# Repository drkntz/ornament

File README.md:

# ornament
This project is a pic16f1832X-based project to run APA102-2020 and similar two-wire serial RGB LEDs. 

# Schematic rev 1

# PCB Layout rev 1

# PCB 3-D Model rev 1

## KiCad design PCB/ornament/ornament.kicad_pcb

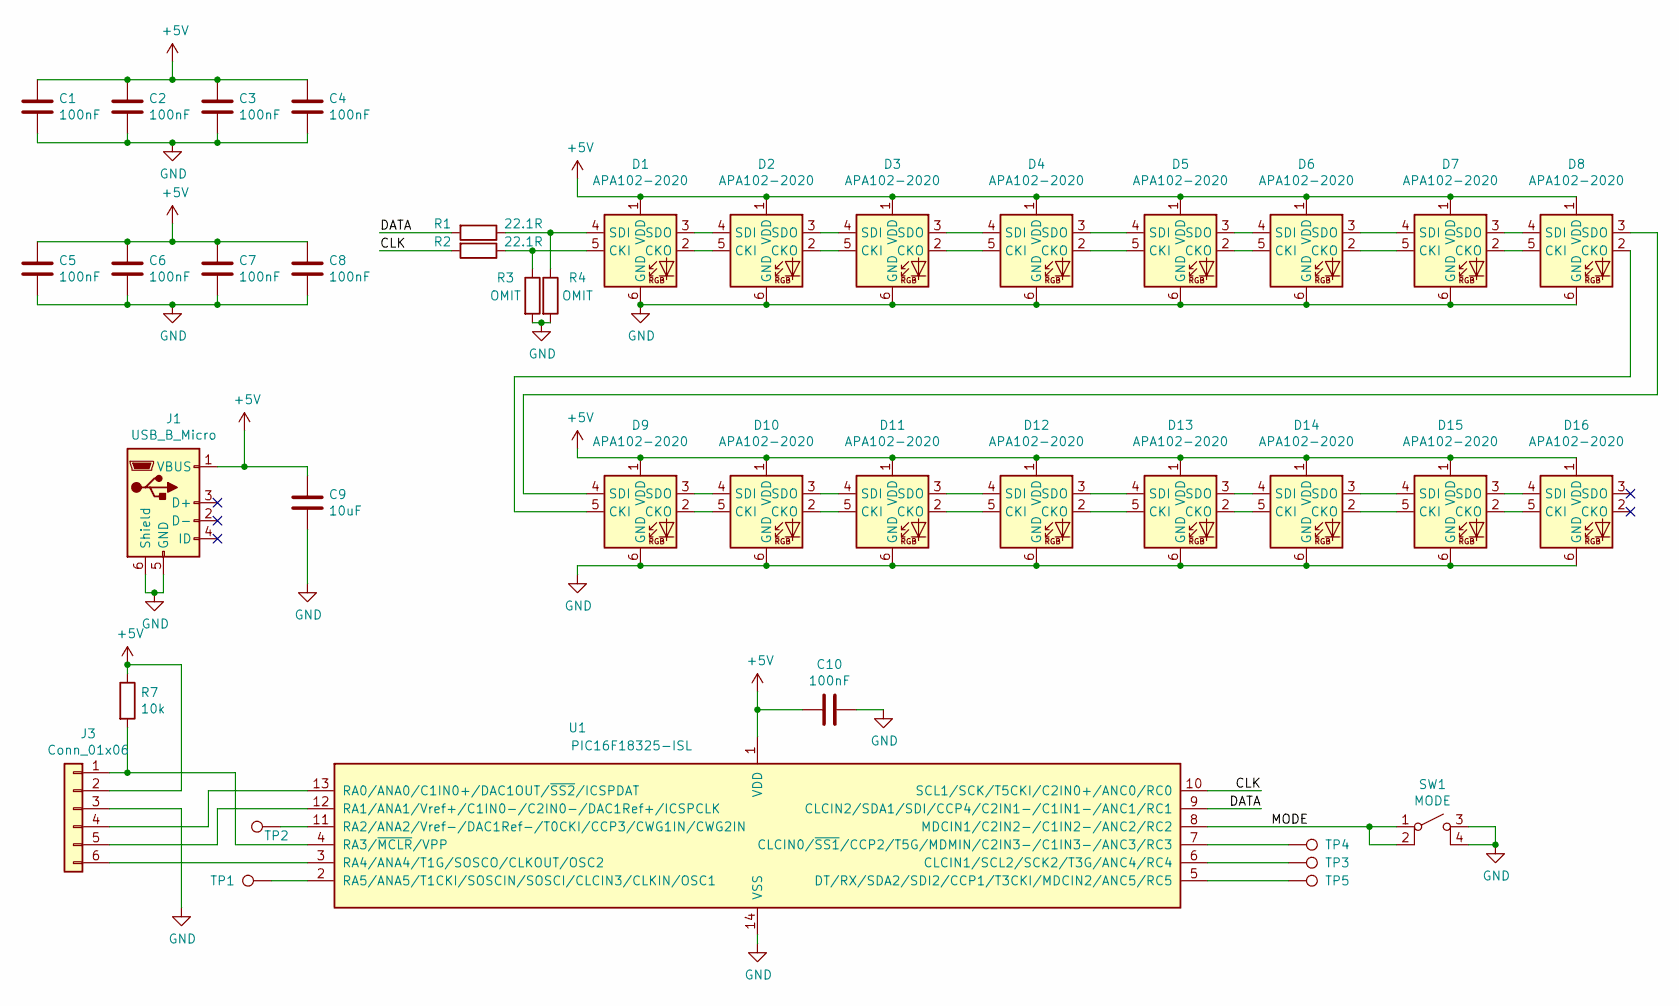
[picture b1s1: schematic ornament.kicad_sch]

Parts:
C1, C2, C3, C4, C5, C6, C7, C8, C10: 100nF; C_0805_2012Metric
C9: 10uF; C_0805_2012Metric
D1, D2, D3, D4, D5, D6, D7, D8, D9, D10, D11, D12, D13, D14, D15, D16: APA102-2020; LED-APA102-2020
J1: USB_B_Micro; USB_Micro-B_Molex-105017-0001
J3: Conn_01x06; Tag-Connect_TC2030-IDC-FP_2x03_P1.27mm_Vertical
R1, R2: 22.1R; R_0805_2012Metric
R3, R4: OMIT; R_0805_2012Metric
R7: 10k; R_0805_2012Metric
SW1: MODE; SW_SPST_Omron_B3FS-101xP
TP1: TP1; TestPoint_Plated_Hole_D2.0mm
TP2: TP2; TestPoint_Plated_Hole_D2.0mm
TP3: TP3; TestPoint_Plated_Hole_D2.0mm
TP4: TP4; TestPoint_Plated_Hole_D2.0mm
TP5: TP5; TestPoint_Plated_Hole_D2.0mm
U1: PIC16F18325-ISL; SOIC-14_3.9x8.7mm_P1.27mm

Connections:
+5V: C1.1, C2.1, C3.1, C4.1, C5.1, C6.1, C7.1, C8.1, C9.1, C10.2, D1.1 (VDD), D2.1 (VDD), D3.1 (VDD), D4.1 (VDD), D5.1 (VDD), D6.1 (VDD), D7.1 (VDD), D8.1 (VDD), D9.1 (VDD), D10.1 (VDD), D11.1 (VDD), D12.1 (VDD), D13.1 (VDD), D14.1 (VDD), D15.1 (VDD), D16.1 (VDD), J1.1 (VBUS), J3.2, R7.1, U1.1 (VDD)
/CLK: R2.2, U1.10 (SCL1/SCK/T5CKI/C2IN0+/ANC0/RC0)
/DATA: R1.2, U1.9 (CLCIN2/SDA1/SDI/CCP4/C2IN1-/C1IN1-/ANC1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)
/MODE: SW1.1 (A), SW1.2 (A1), U1.8 (MDCIN1/C2IN2-/C1IN2-/ANC2/RC2)
GND: C1.2, C2.2, C3.2, C4.2, C5.2, C6.2, C7.2, C8.2, C9.2, C10.1, D1.6 (GND), D2.6 (GND), D3.6 (GND), D4.6 (GND), D5.6 (GND), D6.6 (GND), D7.6 (GND), D8.6 (GND), D9.6 (GND), D10.6 (GND), D11.6 (GND), D12.6 (GND), D13.6 (GND), D14.6 (GND), D15.6 (GND), D16.6 (GND), J1.5 (GND), J1.6 (Shield), J3.3, R3.2, R4.2, SW1.3 (B), SW1.4 (B1), U1.14 (VSS)
unnamed: D1.2 (CKO), D2.5 (CKI)
unnamed: D1.3 (SDO), D2.4 (SDI)
unnamed: D1.4 (SDI), R1.1, R4.1
unnamed: D1.5 (CKI), R2.1, R3.1
unnamed: D2.2 (CKO), D3.5 (CKI)
unnamed: D2.3 (SDO), D3.4 (SDI)
unnamed: D3.2 (CKO), D4.5 (CKI)
unnamed: D3.3 (SDO), D4.4 (SDI)
unnamed: D4.2 (CKO), D5.5 (CKI)
unnamed: D4.3 (SDO), D5.4 (SDI)
unnamed: D5.2 (CKO), D6.5 (CKI)
unnamed: D5.3 (SDO), D6.4 (SDI)
unnamed: D6.2 (CKO), D7.5 (CKI)
unnamed: D6.3 (SDO), D7.4 (SDI)
unnamed: D7.2 (CKO), D8.5 (CKI)
unnamed: D7.3 (SDO), D8.4 (SDI)
unnamed: D8.2 (CKO), D9.5 (CKI)
unnamed: D8.3 (SDO), D9.4 (SDI)
unnamed: D10.2 (CKO), D11.5 (CKI)
unnamed: D10.3 (SDO), D11.4 (SDI)
unnamed: D9.3 (SDO), D10.4 (SDI)
unnamed: D9.2 (CKO), D10.5 (CKI)
unnamed: D11.2 (CKO), D12.5 (CKI)
unnamed: D11.3 (SDO), D12.4 (SDI)
unnamed: D12.2 (CKO), D13.5 (CKI)
unnamed: D12.3 (SDO), D13.4 (SDI)
unnamed: D13.2 (CKO), D14.5 (CKI)
unnamed: D13.3 (SDO), D14.4 (SDI)
unnamed: D14.2 (CKO), D15.5 (CKI)
unnamed: D14.3 (SDO), D15.4 (SDI)
unnamed: D15.2 (CKO), D16.5 (CKI)
unnamed: D15.3 (SDO), D16.4 (SDI)
unnamed: J3.1, R7.2, U1.4 (RA3/~MCLR/VPP)
unnamed: J3.4, U1.13 (RA0/ANA0/C1IN0+/DAC1OUT/~SS2/ICSPDAT)
unnamed: J3.5, U1.12 (RA1/ANA1/Vref+/C1IN0-/C2IN0-/DAC1Ref+/I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)
unnamed: J3.6, U1.3 (RA4/ANA4/T1G/SOSCO/CLKOUT/OSC2)
unnamed: TP1.1, U1.2 (RA5/ANA5/T1CKI/SOSCIN/SOSCI/CLCIN3/CLKI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)
unnamed: TP2.1, U1.11 (RA2/ANA2/Vref-/DAC1Ref-/T0CKI/CCP3/CWG1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)
unnamed: TP3.1, U1.6 (CLCIN1/SCL2/SCK2/T3G/ANC4/RC4)
unnamed: TP4.1, U1.7 (CLCIN0/~SS1/CCP2/T5G/MDMIN/C2IN3-/C1IN3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)
unnamed: TP5.1, U1.5 (DT/RX/SDA2/SDI2/CCP1/T3CKI/MDCIN2/ANC5/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)

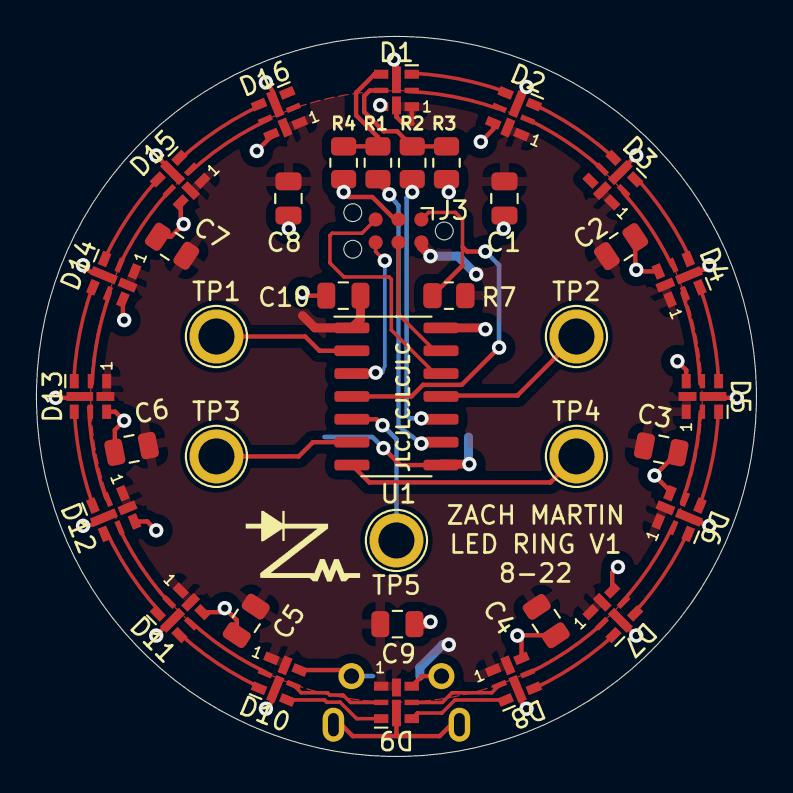
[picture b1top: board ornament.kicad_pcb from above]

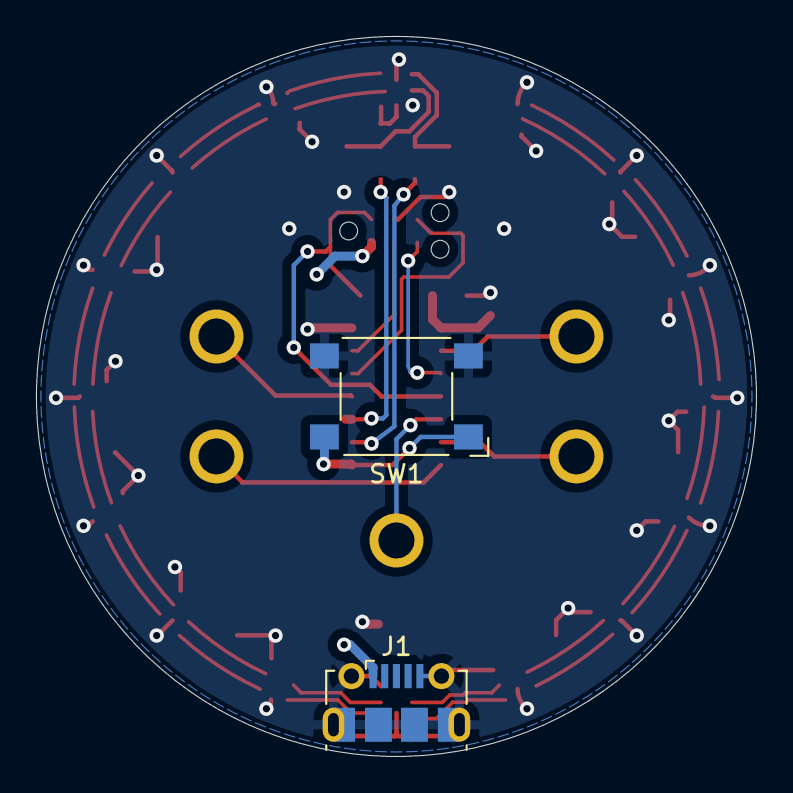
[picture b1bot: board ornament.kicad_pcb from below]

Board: 2 copper layers, 40.0 x 40.0 mm, 40 parts (2 on the bottom side), 46 nets.

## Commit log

2022-08-17 printouts
2022-08-17 adding dotstar module
2022-08-17 adding firmware
2022-08-17 bug fix
2022-08-18 routed PCB, about to upgrade kicad
2022-08-18 updated screenshots
2022-10-16 Update documentation, update firmware, add gerbers
